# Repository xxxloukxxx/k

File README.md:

# Keebs

## Ada36(c)/38

## Chiffre36

## Mad34

## Madeline36

## Mad36v3

---

> [!NOTE]
>
> À tester
>
> ```
> ["Q","W","E","R","T","Y","U","I","O",{w:1.75},"Caps Lock","Home","PgUp"],
> [{w:1.25},"Ctrl","S","D","F","G","H","J","K","L",{x:0.25,a:7,w:1.25,h:2,w2:1.5,h2:1,x2:-0.25},"",{a:4},"End","PgDn"],
> [{w:1.5},"Tab","X","C","V","B","N","M","<\n,",">\n.",{x:1.25},"Insert","Delete"],
> ["Esc",{w:1.25},"Alt",{x:5.75,w:1.25},"Alt",{w:1.5},"|\n\\","~\n`","Z"],
> [{y:-0.75,x:2.5,w:2.75},"Shift",{x:0.25,w:2.25},"Enter"]
> ```

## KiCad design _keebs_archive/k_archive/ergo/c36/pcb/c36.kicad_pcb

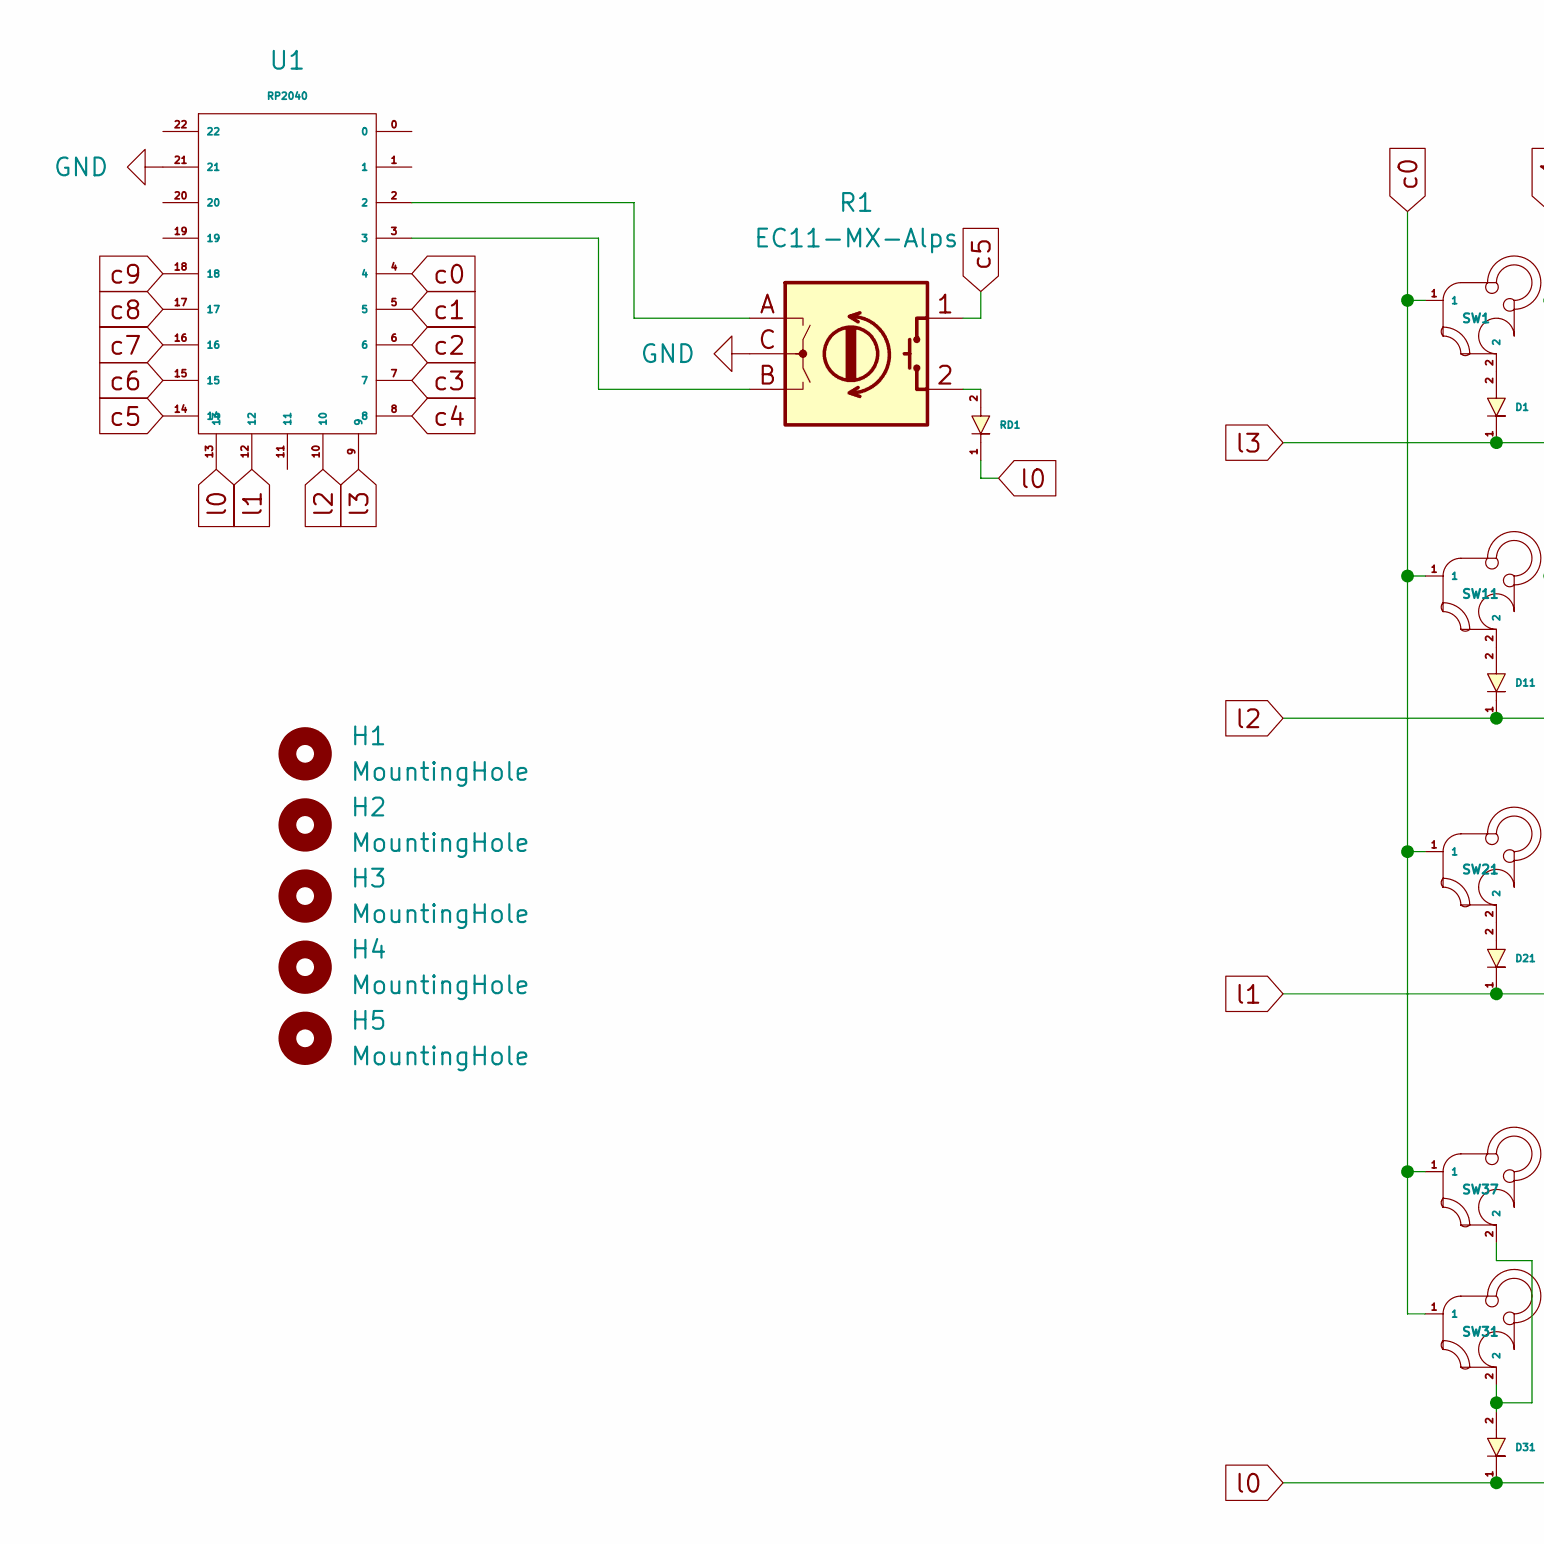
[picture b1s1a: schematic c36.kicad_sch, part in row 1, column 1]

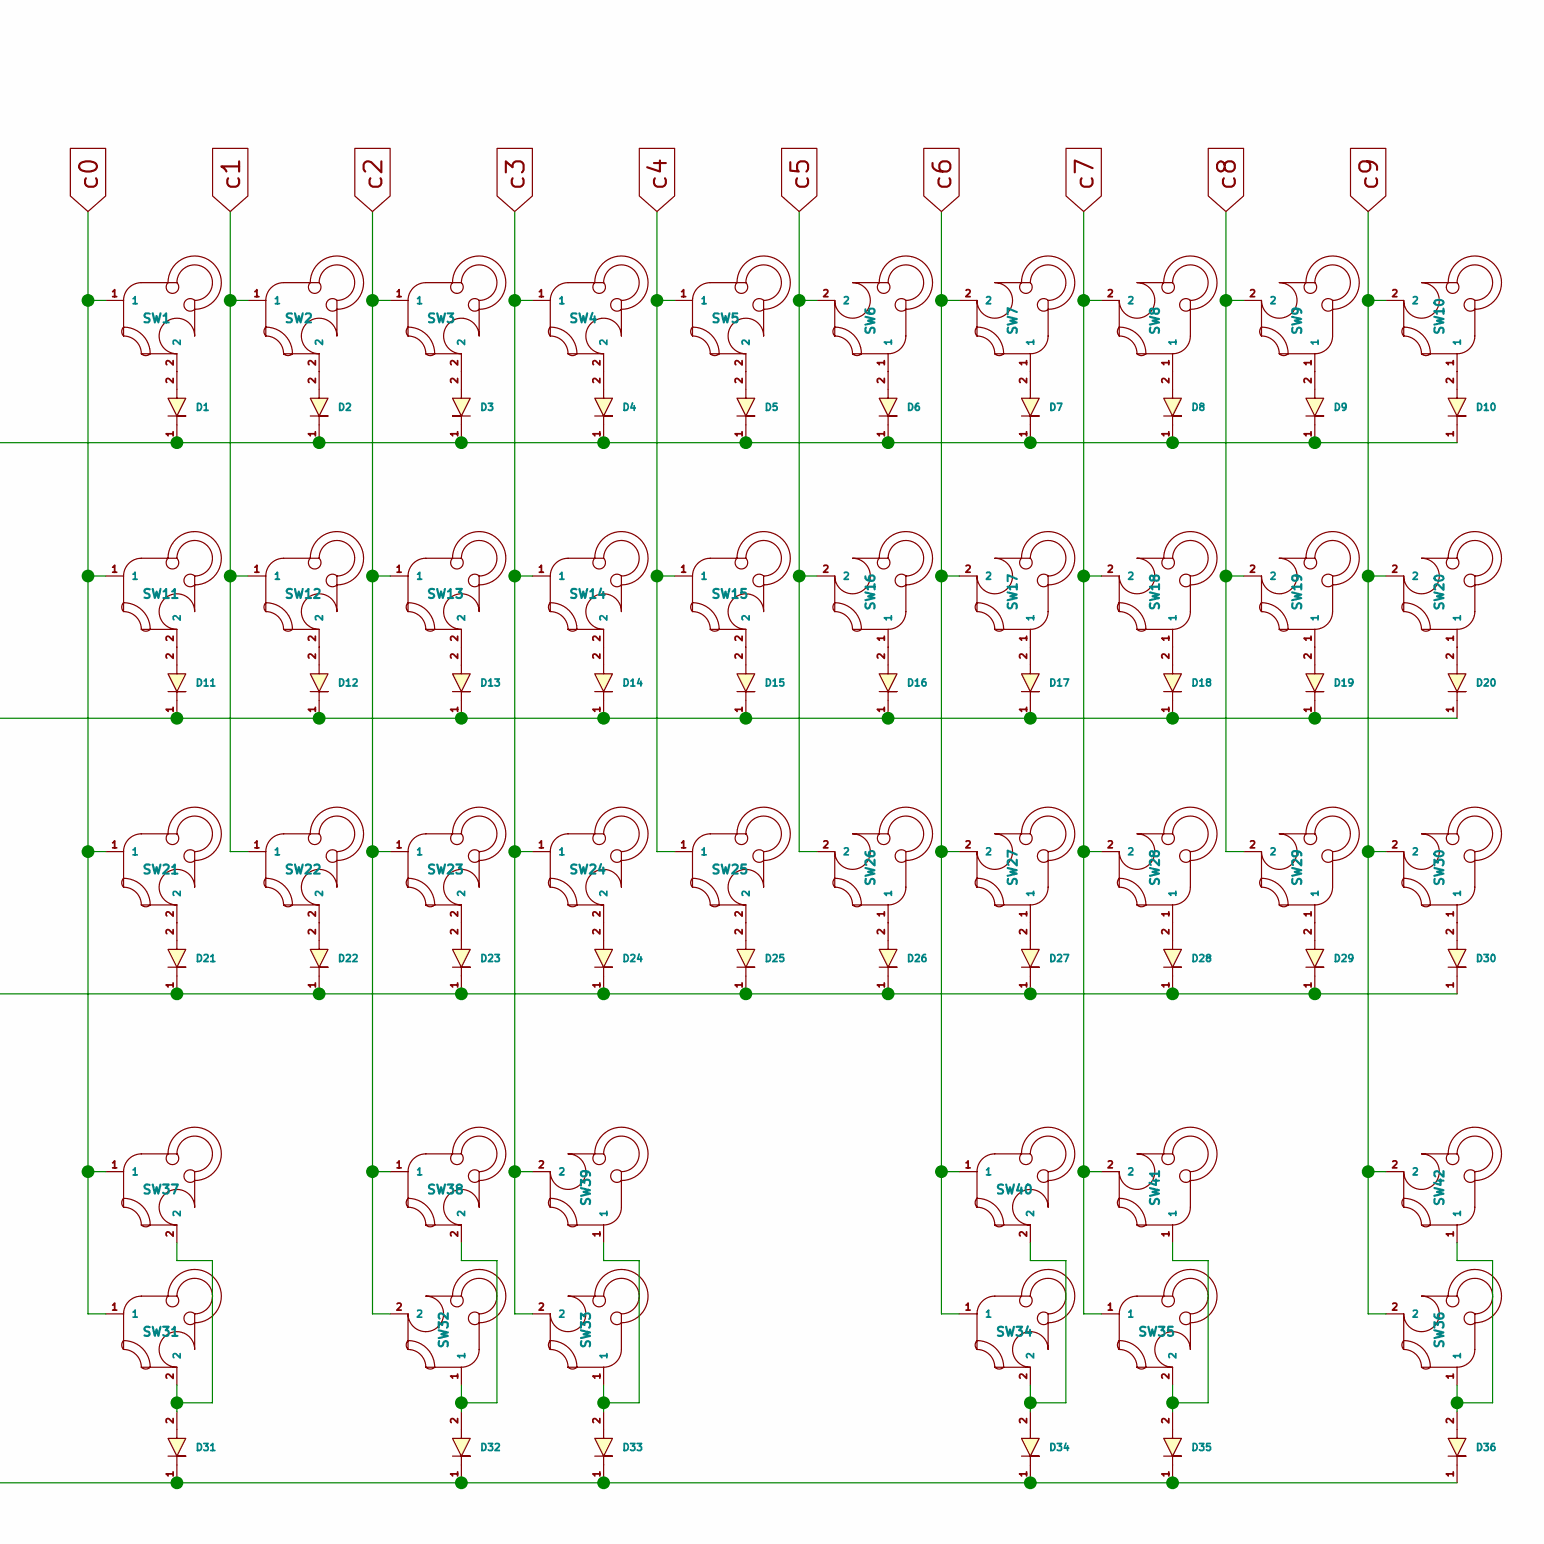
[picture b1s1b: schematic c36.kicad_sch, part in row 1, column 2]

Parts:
D1, D2, D3, D4, D5, D6, D7, D8, D9, D10, D11, D12, D13, D14, D15, D16, D17, D18, D19, D20, D21, D22, D23, D24, D25, D26, D27, D28, D29, D30, D31, D32, D33, D34, D35, D36: Diode
H1, H2, H3, H4, H5: MountingHole; MountingHole_2.2mm_M2
R1: EC11-MX-Alps; RotaryEncoder_EC11
RD1: Diode
SW1, SW2, SW3, SW4, SW5, SW6, SW7, SW8, SW9, SW10, SW11, SW12, SW13, SW14, SW15, SW16, SW17, SW18, SW19, SW20, SW21, SW22, SW23, SW24, SW25, SW26, SW27, SW28, SW29, SW30, SW31, SW32, SW33, SW34, SW35, SW36, SW37, SW38, SW39, SW40, SW41, SW42: key; MX-5pin
U1: RP2040

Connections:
GND: R1.C, U1.21
unnamed: D1.2, SW1.2
unnamed: D2.2, SW2.2
unnamed: D3.2, SW3.2
unnamed: D4.2, SW4.2
unnamed: D5.2, SW5.2
unnamed: D6.2, SW6.1
unnamed: D7.2, SW7.1
unnamed: D8.2, SW8.1
unnamed: D9.2, SW9.1
unnamed: D10.2, SW10.1
unnamed: D11.2, SW11.2
unnamed: D12.2, SW12.2
unnamed: D13.2, SW13.2
unnamed: D14.2, SW14.2
unnamed: D15.2, SW15.2
unnamed: D16.2, SW16.1
unnamed: D17.2, SW17.1
unnamed: D18.2, SW18.1
unnamed: D19.2, SW19.1
unnamed: D20.2, SW20.1
unnamed: D21.2, SW21.2
unnamed: D22.2, SW22.2
unnamed: D23.2, SW23.2
unnamed: D24.2, SW24.2
unnamed: D25.2, SW25.2
unnamed: D26.2, SW26.1
unnamed: D27.2, SW27.1
unnamed: D28.2, SW28.1
unnamed: D29.2, SW29.1
unnamed: D30.2, SW30.1
unnamed: D31.2, SW31.2, SW37.2
unnamed: D32.2, SW32.1, SW38.2
unnamed: D33.2, SW33.1, SW39.1
unnamed: D34.2, SW34.2, SW40.2
unnamed: D35.2, SW35.2, SW41.1
unnamed: D36.2, SW36.1, SW42.1
unnamed: R1.2, RD1.2
unnamed: R1.A, U1.2
unnamed: R1.B, U1.3
c0: SW1.1, SW11.1, SW21.1, SW31.1, SW37.1, U1.4
c1: SW2.1, SW12.1, SW22.1, U1.5
c2: SW3.1, SW13.1, SW23.1, SW32.2, SW38.1, U1.6
c3: SW4.1, SW14.1, SW24.1, SW33.2, SW39.2, U1.7
c4: SW5.1, SW15.1, SW25.1, U1.8
c5: R1.1, SW6.2, SW16.2, SW26.2, U1.14
c6: SW7.2, SW17.2, SW27.2, SW34.1, SW40.1, U1.15
c7: SW8.2, SW18.2, SW28.2, SW35.1, SW41.2, U1.16
c8: SW9.2, SW19.2, SW29.2, U1.17
c9: SW10.2, SW20.2, SW30.2, SW36.2, SW42.2, U1.18
l0: D31.1, D32.1, D33.1, D34.1, D35.1, D36.1, RD1.1, U1.13
l1: D21.1, D22.1, D23.1, D24.1, D25.1, D26.1, D27.1, D28.1, D29.1, D30.1, U1.12
l2: D11.1, D12.1, D13.1, D14.1, D15.1, D16.1, D17.1, D18.1, D19.1, D20.1, U1.10
l3: D1.1, D2.1, D3.1, D4.1, D5.1, D6.1, D7.1, D8.1, D9.1, D10.1, U1.9

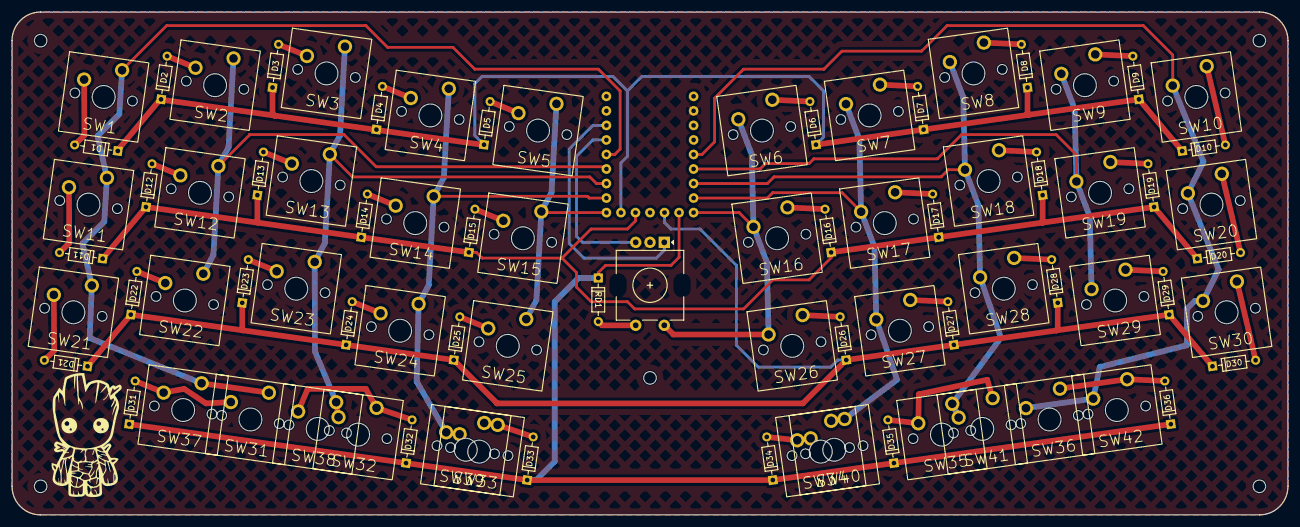
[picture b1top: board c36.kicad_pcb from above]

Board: 2 copper layers, 223.0 x 87.9 mm, 86 parts (1 on the bottom side), 54 nets.

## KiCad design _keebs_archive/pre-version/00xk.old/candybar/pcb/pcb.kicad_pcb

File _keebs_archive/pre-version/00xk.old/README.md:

# Des keyboards qui vont presque bien :)

- [000k](https://github.com/xxxloukxxx/00xk/tree/main/000k) : Un 40%++, pas ergo, avec une ligne en plus inspiré
- [001k](https://github.com/xxxloukxxx/00xk/tree/main/001k) : Un ergo en 3x12+5, inspiré de revuing 41
- [002k](https://github.com/xxxloukxxx/00xk/tree/main/002k) : Un ergo en 3x12+6, inspiré de revuing 41 ... encore
- [003k](https://github.com/xxxloukxxx/00xk/tree/main/003k) : Un ergo en 4x12, inspiré de revuing 41 ... encore/encore
- [004k](https://github.com/xxxloukxxx/00xk/tree/main/004k) : Un ergo 52, inspiré de HillSide52
- [005k](https://github.com/xxxloukxxx/00xk/tree/main/005k) : 001k mais avec une derniere ligne un peu plus badass
- [006k](https://github.com/xxxloukxxx/00xk/tree/main/006k) : Feker Alice 80
- [007k](https://github.com/xxxloukxxx/00xk/tree/main/007k) : Un petit "Explode" 4 Gigi

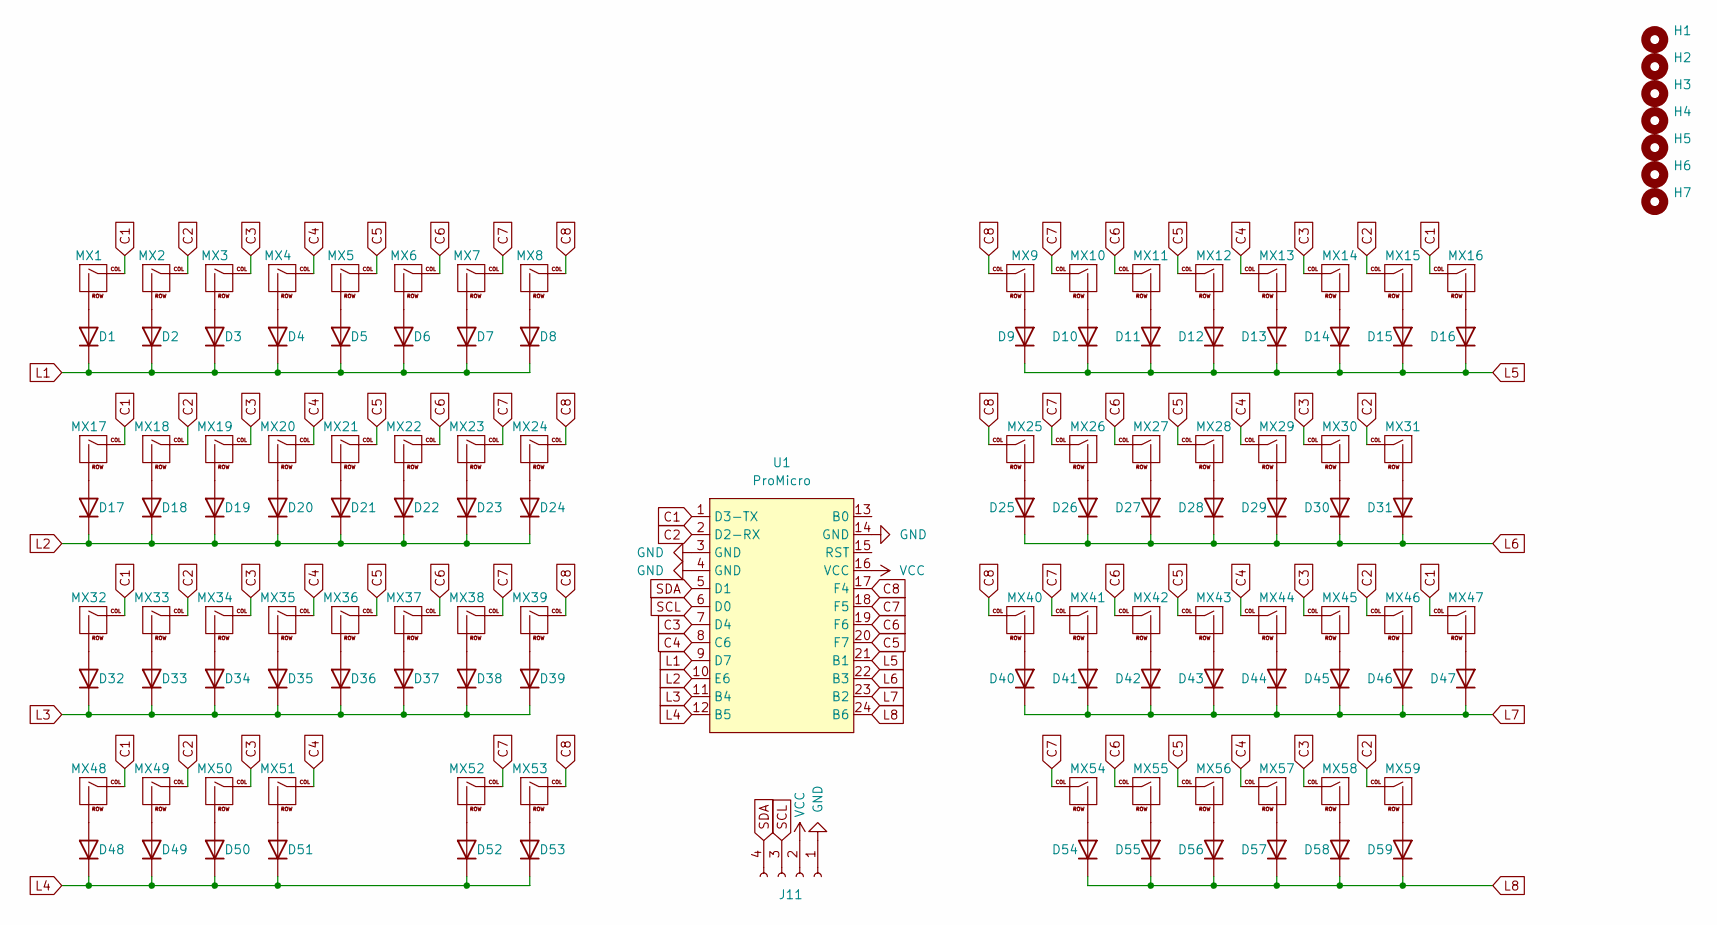
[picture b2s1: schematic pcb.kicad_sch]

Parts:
D1, D2, D3, D4, D5, D6, D7, D8, D9, D10, D11, D12, D13, D14, D15, D16, D17, D18, D19, D20, D21, D22, D23, D24, D25, D26, D27, D28, D29, D30, D31, D32, D33, D34, D35, D36, D37, D38, D39, D40, D41, D42, D43, D44, D45, D46, D47, D48, D49, D50, D51, D52, D53, D54, D55, D56, D57, D58, D59: 1N4148; D_DO-35_SOD27_P7.62mm_Horizontal
H1, H2, H3, H4, H5, H6, H7: MountingHole; MountingHole_2.2mm_M2
J11: Conn_01x04_Socket; SSD1306-0.91-OLED-4pin-128x32
MX1, MX2, MX3, MX4, MX5, MX6, MX7, MX8, MX9, MX10, MX11, MX12, MX13, MX14, MX15, MX16, MX18, MX19, MX20, MX21, MX22, MX23, MX24, MX25, MX26, MX28, MX29, MX30, MX31, MX33, MX34, MX35, MX36, MX37, MX38, MX39, MX40, MX41, MX43, MX44, MX45, MX46, MX49, MX55, MX56, MX57, MX58, MX59: MX; MX-Alps-Hybrid-1U
MX17, MX42, MX48, MX50, MX53, MX54: MX; MX-Alps-Hybrid-1.25U
MX27, MX32: MX; MX-Alps-Hybrid-1.75U
MX47: MX; MX-Alps-Hybrid-2U-Vertical
MX51: MX; MX-Alps-Hybrid-2.75U-ReversedStabilizers
MX52: MX; MX-Alps-Hybrid-2.25U-ReversedStabilizers
U1: ProMicro; ProMicro_USBup

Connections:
C1: MX1.1 (COL), MX16.1 (COL), MX17.1 (COL), MX32.1 (COL), MX47.1 (COL), MX48.1 (COL), U1.1 (D3-TX)
C2: MX2.1 (COL), MX15.1 (COL), MX18.1 (COL), MX31.1 (COL), MX33.1 (COL), MX46.1 (COL), MX49.1 (COL), MX59.1 (COL), U1.2 (D2-RX)
C3: MX3.1 (COL), MX14.1 (COL), MX19.1 (COL), MX30.1 (COL), MX34.1 (COL), MX45.1 (COL), MX50.1 (COL), MX58.1 (COL), U1.7 (D4)
C4: MX4.1 (COL), MX13.1 (COL), MX20.1 (COL), MX29.1 (COL), MX35.1 (COL), MX44.1 (COL), MX51.1 (COL), MX57.1 (COL), U1.8 (C6)
C5: MX5.1 (COL), MX12.1 (COL), MX21.1 (COL), MX28.1 (COL), MX36.1 (COL), MX43.1 (COL), MX56.1 (COL), U1.20 (F7)
C6: MX6.1 (COL), MX11.1 (COL), MX22.1 (COL), MX27.1 (COL), MX37.1 (COL), MX42.1 (COL), MX55.1 (COL), U1.19 (F6)
C7: MX7.1 (COL), MX10.1 (COL), MX23.1 (COL), MX26.1 (COL), MX38.1 (COL), MX41.1 (COL), MX52.1 (COL), MX54.1 (COL), U1.18 (F5)
C8: MX8.1 (COL), MX9.1 (COL), MX24.1 (COL), MX25.1 (COL), MX39.1 (COL), MX40.1 (COL), MX53.1 (COL), U1.17 (F4)
GND: J11.1, U1.3 (GND), U1.4 (GND), U1.14 (GND)
L1: D1.1 (K), D2.1 (K), D3.1 (K), D4.1 (K), D5.1 (K), D6.1 (K), D7.1 (K), D8.1 (K), U1.9 (D7)
L2: D17.1 (K), D18.1 (K), D19.1 (K), D20.1 (K), D21.1 (K), D22.1 (K), D23.1 (K), D24.1 (K), U1.10 (E6)
L3: D32.1 (K), D33.1 (K), D34.1 (K), D35.1 (K), D36.1 (K), D37.1 (K), D38.1 (K), D39.1 (K), U1.11 (B4)
L4: D48.1 (K), D49.1 (K), D50.1 (K), D51.1 (K), D52.1 (K), D53.1 (K), U1.12 (B5)
L5: D9.1 (K), D10.1 (K), D11.1 (K), D12.1 (K), D13.1 (K), D14.1 (K), D15.1 (K), D16.1 (K), U1.21 (B1)
L6: D25.1 (K), D26.1 (K), D27.1 (K), D28.1 (K), D29.1 (K), D30.1 (K), D31.1 (K), U1.22 (B3)
L7: D40.1 (K), D41.1 (K), D42.1 (K), D43.1 (K), D44.1 (K), D45.1 (K), D46.1 (K), D47.1 (K), U1.23 (B2)
L8: D54.1 (K), D55.1 (K), D56.1 (K), D57.1 (K), D58.1 (K), D59.1 (K), U1.24 (B6)
unnamed: D1.2 (A), MX1.2 (ROW)
unnamed: D2.2 (A), MX2.2 (ROW)
unnamed: D3.2 (A), MX3.2 (ROW)
unnamed: D4.2 (A), MX4.2 (ROW)
unnamed: D5.2 (A), MX5.2 (ROW)
unnamed: D6.2 (A), MX6.2 (ROW)
unnamed: D7.2 (A), MX7.2 (ROW)
unnamed: D8.2 (A), MX8.2 (ROW)
unnamed: D9.2 (A), MX9.2 (ROW)
unnamed: D10.2 (A), MX10.2 (ROW)
unnamed: D11.2 (A), MX11.2 (ROW)
unnamed: D12.2 (A), MX12.2 (ROW)
unnamed: D13.2 (A), MX13.2 (ROW)
unnamed: D14.2 (A), MX14.2 (ROW)
unnamed: D15.2 (A), MX15.2 (ROW)
unnamed: D16.2 (A), MX16.2 (ROW)
unnamed: D17.2 (A), MX17.2 (ROW)
unnamed: D18.2 (A), MX18.2 (ROW)
unnamed: D19.2 (A), MX19.2 (ROW)
unnamed: D20.2 (A), MX20.2 (ROW)
unnamed: D21.2 (A), MX21.2 (ROW)
unnamed: D22.2 (A), MX22.2 (ROW)
unnamed: D23.2 (A), MX23.2 (ROW)
unnamed: D24.2 (A), MX24.2 (ROW)
unnamed: D25.2 (A), MX25.2 (ROW)
unnamed: D26.2 (A), MX26.2 (ROW)
unnamed: D27.2 (A), MX27.2 (ROW)
unnamed: D28.2 (A), MX28.2 (ROW)
unnamed: D29.2 (A), MX29.2 (ROW)
unnamed: D30.2 (A), MX30.2 (ROW)
unnamed: D31.2 (A), MX31.2 (ROW)
unnamed: D32.2 (A), MX32.2 (ROW)
unnamed: D33.2 (A), MX33.2 (ROW)
unnamed: D34.2 (A), MX34.2 (ROW)
unnamed: D35.2 (A), MX35.2 (ROW)
unnamed: D36.2 (A), MX36.2 (ROW)
unnamed: D37.2 (A), MX37.2 (ROW)
unnamed: D38.2 (A), MX38.2 (ROW)
unnamed: D39.2 (A), MX39.2 (ROW)
unnamed: D40.2 (A), MX40.2 (ROW)
unnamed: D41.2 (A), MX41.2 (ROW)
unnamed: D42.2 (A), MX42.2 (ROW)
unnamed: D43.2 (A), MX43.2 (ROW)
unnamed: D44.2 (A), MX44.2 (ROW)
unnamed: D45.2 (A), MX45.2 (ROW)
unnamed: D46.2 (A), MX46.2 (ROW)
unnamed: D47.2 (A), MX47.2 (ROW)
unnamed: D48.2 (A), MX48.2 (ROW)
unnamed: D49.2 (A), MX49.2 (ROW)
unnamed: D50.2 (A), MX50.2 (ROW)
unnamed: D51.2 (A), MX51.2 (ROW)
unnamed: D52.2 (A), MX52.2 (ROW)
unnamed: D53.2 (A), MX53.2 (ROW)
unnamed: D54.2 (A), MX54.2 (ROW)
unnamed: D55.2 (A), MX55.2 (ROW)
unnamed: D56.2 (A), MX56.2 (ROW)
unnamed: D57.2 (A), MX57.2 (ROW)
unnamed: D58.2 (A), MX58.2 (ROW)
unnamed: D59.2 (A), MX59.2 (ROW)
SCL: J11.3, U1.6 (D0)
SDA: J11.4, U1.5 (D1)
VCC: J11.2, U1.16 (VCC)

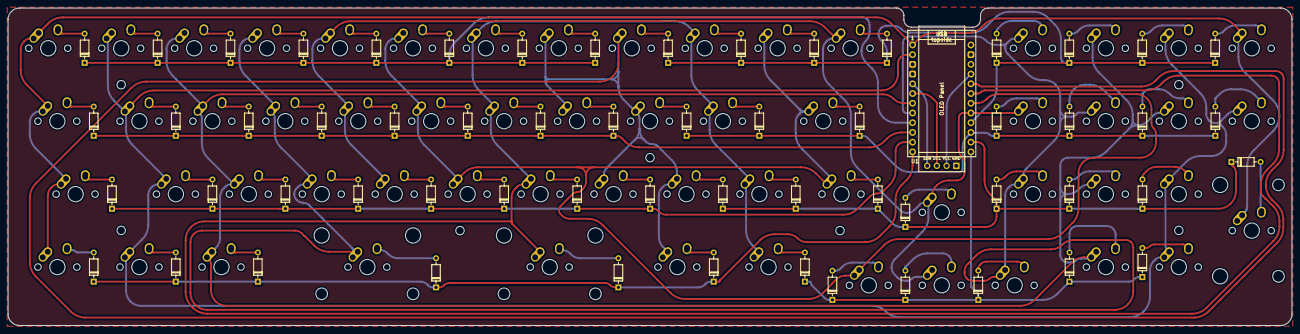
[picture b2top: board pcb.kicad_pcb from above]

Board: 2 copper layers, 335.3 x 82.9 mm, 127 parts (0 on the bottom side), 79 nets.

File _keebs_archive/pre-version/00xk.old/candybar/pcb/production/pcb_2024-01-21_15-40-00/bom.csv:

Designator,Footprint,Quantity,Value,LCSC Part #
"D1, D10, D11, D12, D13, D14, D15, D16, D17, D18, D19, D2, D20, D21, D22, D23, D24, D25, D26, D27, D28, D29, D3, D30, D31, D32, D33, D34, D35, D36, D37, D38, D39, D4, D40, D41, D42, D43, D44, D45, D46, D47, D48, D49, D5, D50, D51, D52, D53, D54, D55, D56, D57, D58, D59, D6, D7, D8, D9",D_DO-35_SOD27_P7.62mm_Horizontal,59,1N4148,
"H1, H2, H3, H4, H5, H6, H7",MountingHole_2.2mm_M2,7,MountingHole,
J11,SSD1306-0.91-OLED-4pin-128x32,1,Conn_01x04_Socket,
"MX1, MX10, MX11, MX12, MX13, MX14, MX15, MX16, MX18, MX19, MX2, MX20, MX21, MX22, MX23, MX24, MX25, MX26, MX28, MX29, MX3, MX30, MX31, MX33, MX34, MX35, MX36, MX37, MX38, MX39, MX4, MX40, MX41, MX43, MX44, MX45, MX46, MX49, MX5, MX55, MX56, MX57, MX58, MX59, MX6, MX7, MX8, MX9",MX-Alps-Hybrid-1U,48,MX,
"MX17, MX42, MX48, MX50, MX53, MX54",MX-Alps-Hybrid-1.25U,6,MX,
"MX27, MX32",MX-Alps-Hybrid-1.75U,2,MX,
MX47,MX-Alps-Hybrid-2U-Vertical,1,MX,
MX51,MX-Alps-Hybrid-2.75U-ReversedStabilizers,1,MX,
MX52,MX-Alps-Hybrid-2.25U-ReversedStabilizers,1,MX,

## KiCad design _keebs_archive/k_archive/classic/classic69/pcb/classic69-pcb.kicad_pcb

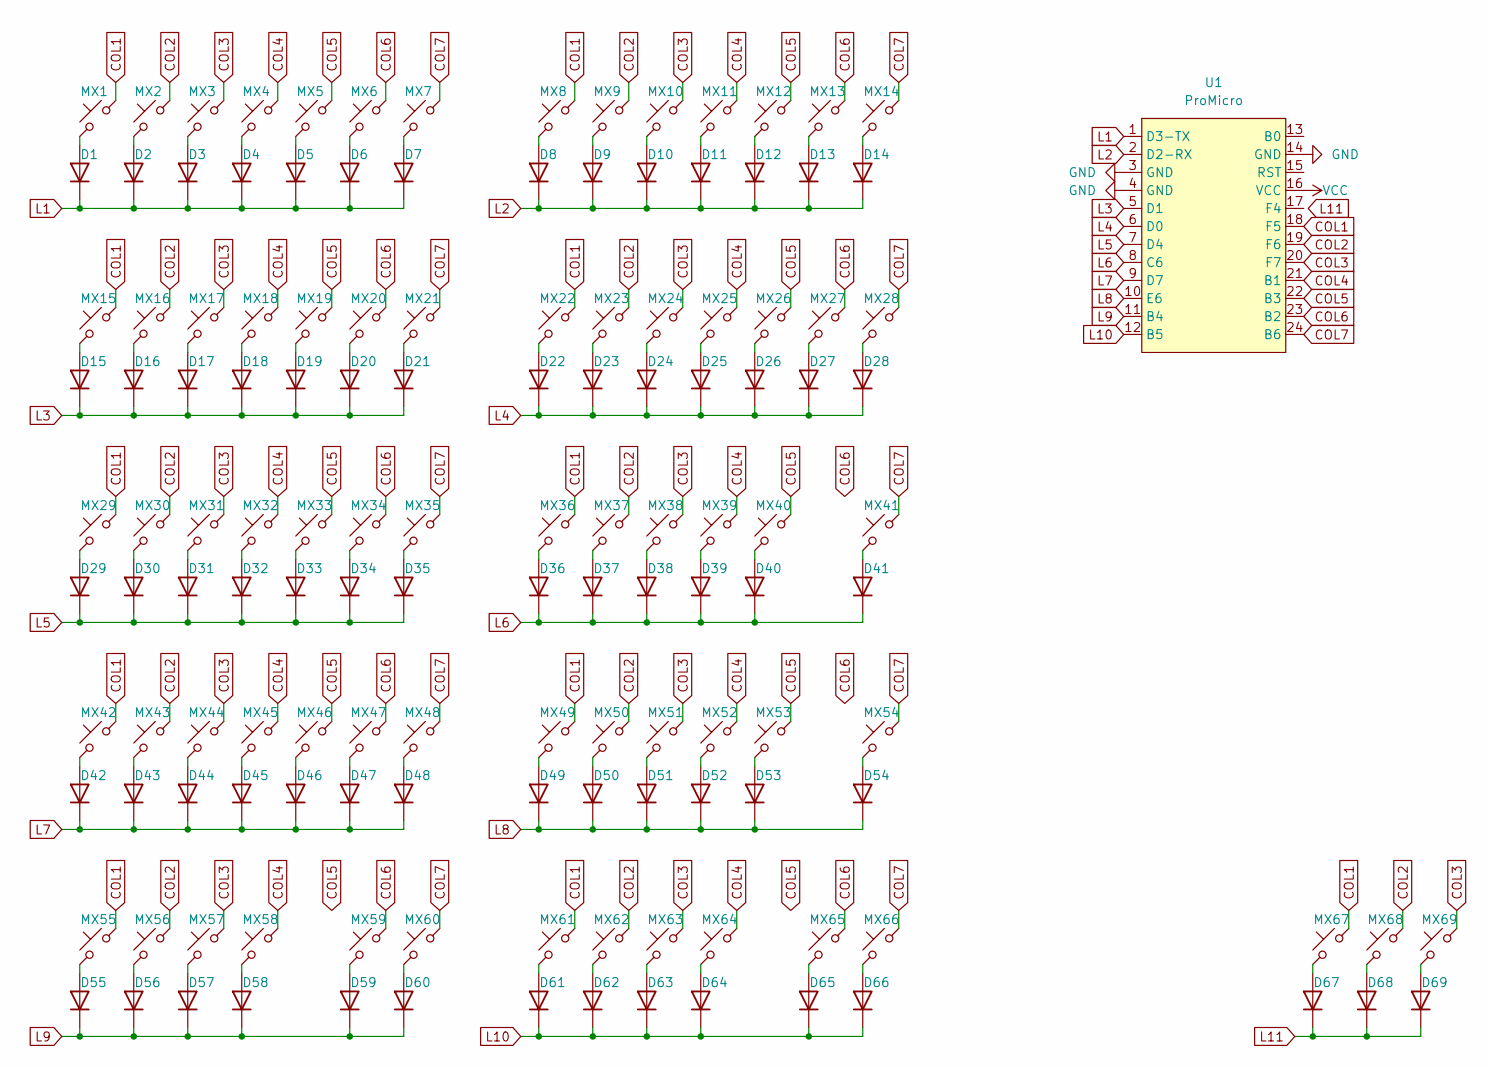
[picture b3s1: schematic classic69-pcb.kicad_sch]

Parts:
D1, D2, D3, D4, D5, D6, D7, D8, D9, D10, D11, D12, D13, D14, D15, D16, D17, D18, D19, D20, D21, D22, D23, D24, D25, D26, D27, D28, D29, D30, D31, D32, D33, D34, D35, D36, D37, D38, D39, D40, D41, D42, D43, D44, D45, D46, D47, D48, D49, D50, D51, D52, D53, D54, D55, D56, D57, D58, D59, D60, D61, D62, D63, D64, D65, D66, D67, D68, D69: 1N4148; D_DO-35_SOD27_P7.62mm_Horizontal
MX1, MX2, MX3, MX4, MX5, MX6, MX7, MX8, MX9, MX10, MX11, MX12, MX13, MX16, MX17, MX18, MX19, MX20, MX21, MX22, MX23, MX24, MX25, MX26, MX27, MX28, MX30, MX31, MX32, MX33, MX34, MX35, MX36, MX37, MX38, MX39, MX40, MX43, MX44, MX45, MX46, MX47, MX48, MX49, MX50, MX51, MX52, MX54, MX61, MX62, MX63, MX64, MX65, MX66, MX67, MX68, MX69: MX_SW_solder; MX-Alps-Hybrid-1U
MX14, MX15: MX_SW_solder; MX-Alps-Hybrid-1.5U
MX29, MX41, MX53: MX_SW_solder; MX-Alps-Hybrid-1.75U
MX42, MX60: MX_SW_solder; MX-Alps-Hybrid-2.25U
MX55, MX56, MX57, MX59: MX_SW_solder; MX-Alps-Hybrid-1.25U
MX58: MX_SW_solder; MX-Alps-Hybrid-2.75U
U1: ProMicro; ProMicro_USBup

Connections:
COL1: MX1.2, MX8.2, MX15.2, MX22.2, MX29.2, MX36.2, MX42.2, MX49.2, MX55.2, MX61.2, MX67.2, U1.18 (F5)
COL2: MX2.2, MX9.2, MX16.2, MX23.2, MX30.2, MX37.2, MX43.2, MX50.2, MX56.2, MX62.2, MX68.2, U1.19 (F6)
COL3: MX3.2, MX10.2, MX17.2, MX24.2, MX31.2, MX38.2, MX44.2, MX51.2, MX57.2, MX63.2, MX69.2, U1.20 (F7)
COL4: MX4.2, MX11.2, MX18.2, MX25.2, MX32.2, MX39.2, MX45.2, MX52.2, MX58.2, MX64.2, U1.21 (B1)
COL5: MX5.2, MX12.2, MX19.2, MX26.2, MX33.2, MX40.2, MX46.2, MX53.2, U1.22 (B3)
COL6: MX6.2, MX13.2, MX20.2, MX27.2, MX34.2, MX47.2, MX59.2, MX65.2, U1.23 (B2)
COL7: MX7.2, MX14.2, MX21.2, MX28.2, MX35.2, MX41.2, MX48.2, MX54.2, MX60.2, MX66.2, U1.24 (B6)
GND: U1.3 (GND), U1.4 (GND), U1.14 (GND)
L1: D1.1 (K), D2.1 (K), D3.1 (K), D4.1 (K), D5.1 (K), D6.1 (K), D7.1 (K), U1.1 (D3-TX)
L2: D8.1 (K), D9.1 (K), D10.1 (K), D11.1 (K), D12.1 (K), D13.1 (K), D14.1 (K), U1.2 (D2-RX)
L3: D15.1 (K), D16.1 (K), D17.1 (K), D18.1 (K), D19.1 (K), D20.1 (K), D21.1 (K), U1.5 (D1)
L4: D22.1 (K), D23.1 (K), D24.1 (K), D25.1 (K), D26.1 (K), D27.1 (K), D28.1 (K), U1.6 (D0)
L5: D29.1 (K), D30.1 (K), D31.1 (K), D32.1 (K), D33.1 (K), D34.1 (K), D35.1 (K), U1.7 (D4)
L6: D36.1 (K), D37.1 (K), D38.1 (K), D39.1 (K), D40.1 (K), D41.1 (K), U1.8 (C6)
L7: D42.1 (K), D43.1 (K), D44.1 (K), D45.1 (K), D46.1 (K), D47.1 (K), D48.1 (K), U1.9 (D7)
L8: D49.1 (K), D50.1 (K), D51.1 (K), D52.1 (K), D53.1 (K), D54.1 (K), U1.10 (E6)
L9: D55.1 (K), D56.1 (K), D57.1 (K), D58.1 (K), D59.1 (K), D60.1 (K), U1.11 (B4)
L10: D61.1 (K), D62.1 (K), D63.1 (K), D64.1 (K), D65.1 (K), D66.1 (K), U1.12 (B5)
L11: D67.1 (K), D68.1 (K), D69.1 (K)
unnamed: D1.2 (A), MX1.1
unnamed: D2.2 (A), MX2.1
unnamed: D3.2 (A), MX3.1
unnamed: D4.2 (A), MX4.1
unnamed: D5.2 (A), MX5.1
unnamed: D6.2 (A), MX6.1
unnamed: D7.2 (A), MX7.1
unnamed: D8.2 (A), MX8.1
unnamed: D9.2 (A), MX9.1
unnamed: D10.2 (A), MX10.1
unnamed: D11.2 (A), MX11.1
unnamed: D12.2 (A), MX12.1
unnamed: D13.2 (A), MX13.1
unnamed: D14.2 (A), MX14.1
unnamed: D15.2 (A), MX15.1
unnamed: D16.2 (A), MX16.1
unnamed: D17.2 (A), MX17.1
unnamed: D18.2 (A), MX18.1
unnamed: D19.2 (A), MX19.1
unnamed: D20.2 (A), MX20.1
unnamed: D21.2 (A), MX21.1
unnamed: D22.2 (A), MX22.1
unnamed: D23.2 (A), MX23.1
unnamed: D24.2 (A), MX24.1
unnamed: D25.2 (A), MX25.1
unnamed: D26.2 (A), MX26.1
unnamed: D27.2 (A), MX27.1
unnamed: D28.2 (A), MX28.1
unnamed: D29.2 (A), MX29.1
unnamed: D30.2 (A), MX30.1
unnamed: D31.2 (A), MX31.1
unnamed: D32.2 (A), MX32.1
unnamed: D33.2 (A), MX33.1
unnamed: D34.2 (A), MX34.1
unnamed: D35.2 (A), MX35.1
unnamed: D36.2 (A), MX36.1
unnamed: D37.2 (A), MX37.1
unnamed: D38.2 (A), MX38.1
unnamed: D39.2 (A), MX39.1
unnamed: D40.2 (A), MX40.1
unnamed: D41.2 (A), MX41.1
unnamed: D42.2 (A), MX42.1
unnamed: D43.2 (A), MX43.1
unnamed: D44.2 (A), MX44.1
unnamed: D45.2 (A), MX45.1
unnamed: D46.2 (A), MX46.1
unnamed: D47.2 (A), MX47.1
unnamed: D48.2 (A), MX48.1
unnamed: D49.2 (A), MX49.1
unnamed: D50.2 (A), MX50.1
unnamed: D51.2 (A), MX51.1
unnamed: D52.2 (A), MX52.1
unnamed: D53.2 (A), MX53.1
unnamed: D54.2 (A), MX54.1
unnamed: D55.2 (A), MX55.1
unnamed: D56.2 (A), MX56.1
unnamed: D57.2 (A), MX57.1
unnamed: D58.2 (A), MX58.1
unnamed: D59.2 (A), MX59.1
unnamed: D60.2 (A), MX60.1
unnamed: D61.2 (A), MX61.1
unnamed: D62.2 (A), MX62.1
unnamed: D63.2 (A), MX63.1
unnamed: D64.2 (A), MX64.1
unnamed: D65.2 (A), MX65.1
unnamed: D66.2 (A), MX66.1
unnamed: D67.2 (A), MX67.1
unnamed: D68.2 (A), MX68.1
unnamed: D69.2 (A), MX69.1
VCC: U1.16 (VCC)

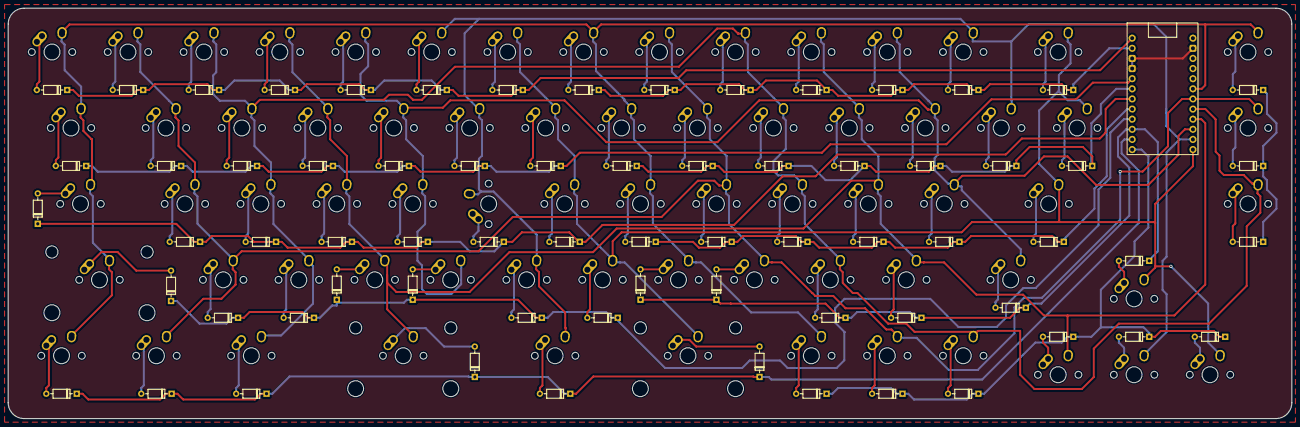
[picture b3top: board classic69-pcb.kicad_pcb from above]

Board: 2 copper layers, 322.0 x 103.0 mm, 139 parts (0 on the bottom side), 88 nets.

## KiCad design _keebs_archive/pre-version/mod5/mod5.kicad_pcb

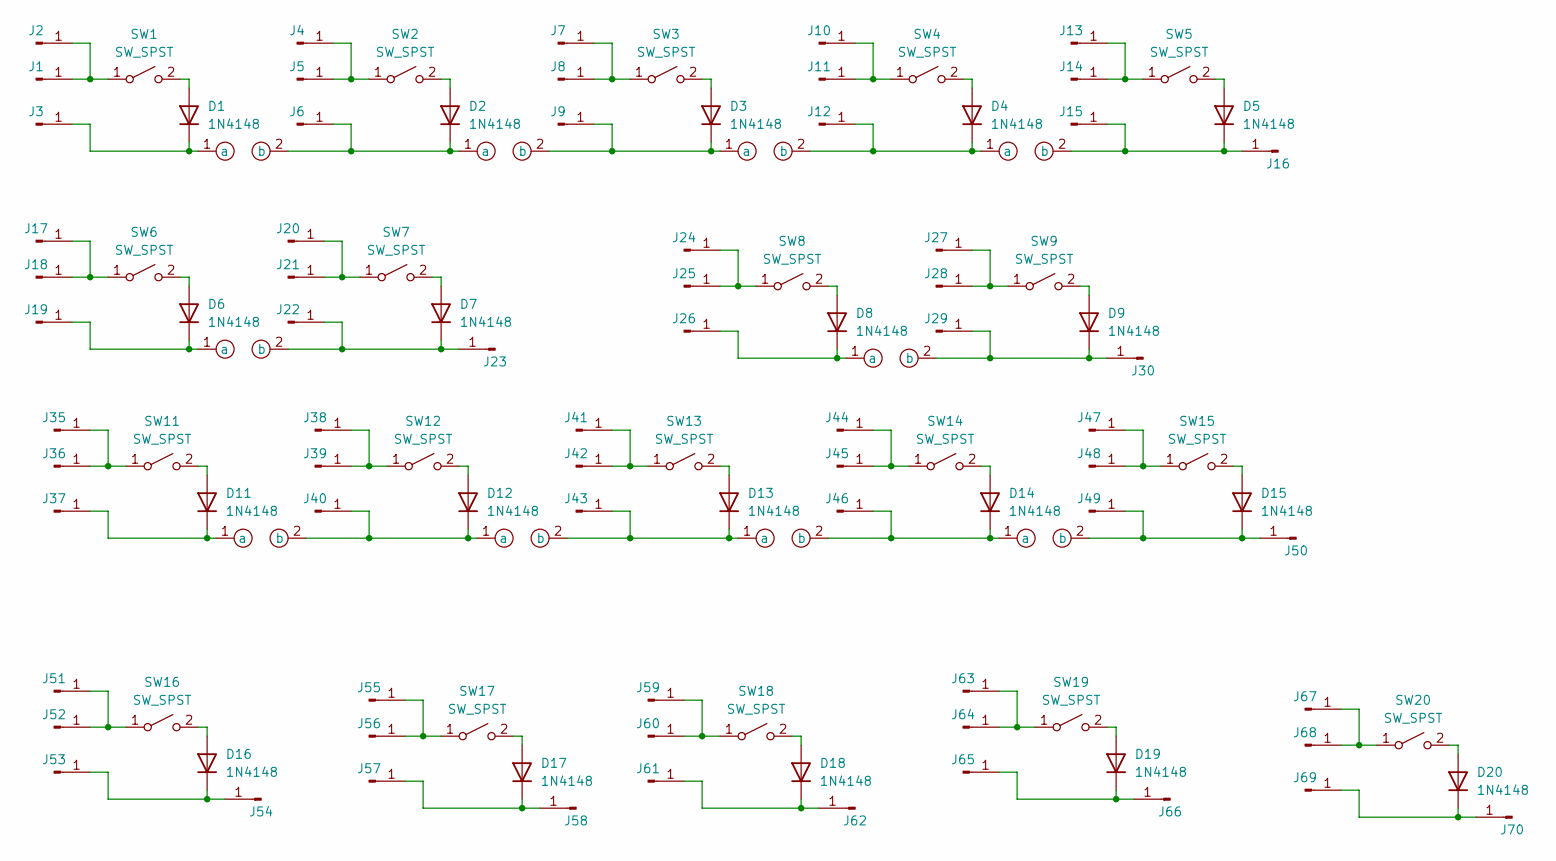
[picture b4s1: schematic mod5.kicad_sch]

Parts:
D1, D2, D3, D4, D5, D6, D7, D8, D9, D11, D12, D13, D14, D15, D16, D17, D18, D19, D20: 1N4148; D_DO-35_SOD27_P7.62mm_Horizontal
J1, J2, J3, J4, J5, J6, J7, J8, J9, J10, J11, J12, J13, J14, J15, J16, J17, J18, J19, J20, J21, J22, J23, J24, J25, J26, J27, J28, J29, J30, J35, J36, J37, J38, J39, J40, J41, J42, J43, J44, J45, J46, J47, J48, J49, J50, J51, J52, J53, J54, J55, J56, J57, J58, J59, J60, J61, J62, J63, J64, J65, J66, J67, J68, J69, J70: Conn_01x01_Pin; conn1x1
P1, P2, P3, P4, P5, P6, P7, P8, P9, P10: pad-footprint
SW1, SW2, SW3, SW4, SW5, SW6, SW7, SW8, SW9, SW11, SW12, SW13, SW14, SW15, SW16, SW17, SW18, SW19, SW20: SW_SPST; SW_Cherry_MX_PCB

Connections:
unnamed: D1.2 (A), SW1.2 (B)
unnamed: D1.1 (K), J3.1, P1.1 (a)
unnamed: D2.2 (A), SW2.2 (B)
unnamed: D2.1 (K), J6.1, P1.2 (b), P2.1 (a)
unnamed: D3.2 (A), SW3.2 (B)
unnamed: D3.1 (K), J9.1, P2.2 (b), P3.1 (a)
unnamed: D4.2 (A), SW4.2 (B)
unnamed: D4.1 (K), J12.1, P3.2 (b), P4.1 (a)
unnamed: D5.2 (A), SW5.2 (B)
unnamed: D5.1 (K), J15.1, J16.1, P4.2 (b)
unnamed: D6.2 (A), SW6.2 (B)
unnamed: D6.1 (K), J19.1, P5.1 (a)
unnamed: D7.2 (A), SW7.2 (B)
unnamed: D7.1 (K), J22.1, J23.1, P5.2 (b)
unnamed: D8.2 (A), SW8.2 (B)
unnamed: D8.1 (K), J26.1, P6.1 (a)
unnamed: D9.2 (A), SW9.2 (B)
unnamed: D9.1 (K), J29.1, J30.1, P6.2 (b)
unnamed: D11.2 (A), SW11.2 (B)
unnamed: D11.1 (K), J37.1, P7.1 (a)
unnamed: D12.2 (A), SW12.2 (B)
unnamed: D12.1 (K), J40.1, P7.2 (b), P8.1 (a)
unnamed: D13.2 (A), SW13.2 (B)
unnamed: D13.1 (K), J43.1, P8.2 (b), P9.1 (a)
unnamed: D14.2 (A), SW14.2 (B)
unnamed: D14.1 (K), J46.1, P9.2 (b), P10.1 (a)
unnamed: D15.2 (A), SW15.2 (B)
unnamed: D15.1 (K), J49.1, J50.1, P10.2 (b)
unnamed: D16.2 (A), SW16.2 (B)
unnamed: D16.1 (K), J53.1, J54.1
unnamed: D17.2 (A), SW17.2 (B)
unnamed: D17.1 (K), J57.1, J58.1
unnamed: D18.2 (A), SW18.2 (B)
unnamed: D18.1 (K), J61.1, J62.1
unnamed: D19.2 (A), SW19.2 (B)
unnamed: D19.1 (K), J65.1, J66.1
unnamed: D20.2 (A), SW20.2 (B)
unnamed: D20.1 (K), J69.1, J70.1
unnamed: J1.1, J2.1, SW1.1 (A)
unnamed: J4.1, J5.1, SW2.1 (A)
unnamed: J7.1, J8.1, SW3.1 (A)
unnamed: J10.1, J11.1, SW4.1 (A)
unnamed: J13.1, J14.1, SW5.1 (A)
unnamed: J17.1, J18.1, SW6.1 (A)
unnamed: J20.1, J21.1, SW7.1 (A)
unnamed: J24.1, J25.1, SW8.1 (A)
unnamed: J27.1, J28.1, SW9.1 (A)
unnamed: J35.1, J36.1, SW11.1 (A)
unnamed: J38.1, J39.1, SW12.1 (A)
unnamed: J41.1, J42.1, SW13.1 (A)
unnamed: J44.1, J45.1, SW14.1 (A)
unnamed: J47.1, J48.1, SW15.1 (A)
unnamed: J51.1, J52.1, SW16.1 (A)
unnamed: J55.1, J56.1, SW17.1 (A)
unnamed: J59.1, J60.1, SW18.1 (A)
unnamed: J63.1, J64.1, SW19.1 (A)
unnamed: J67.1, J68.1, SW20.1 (A)
